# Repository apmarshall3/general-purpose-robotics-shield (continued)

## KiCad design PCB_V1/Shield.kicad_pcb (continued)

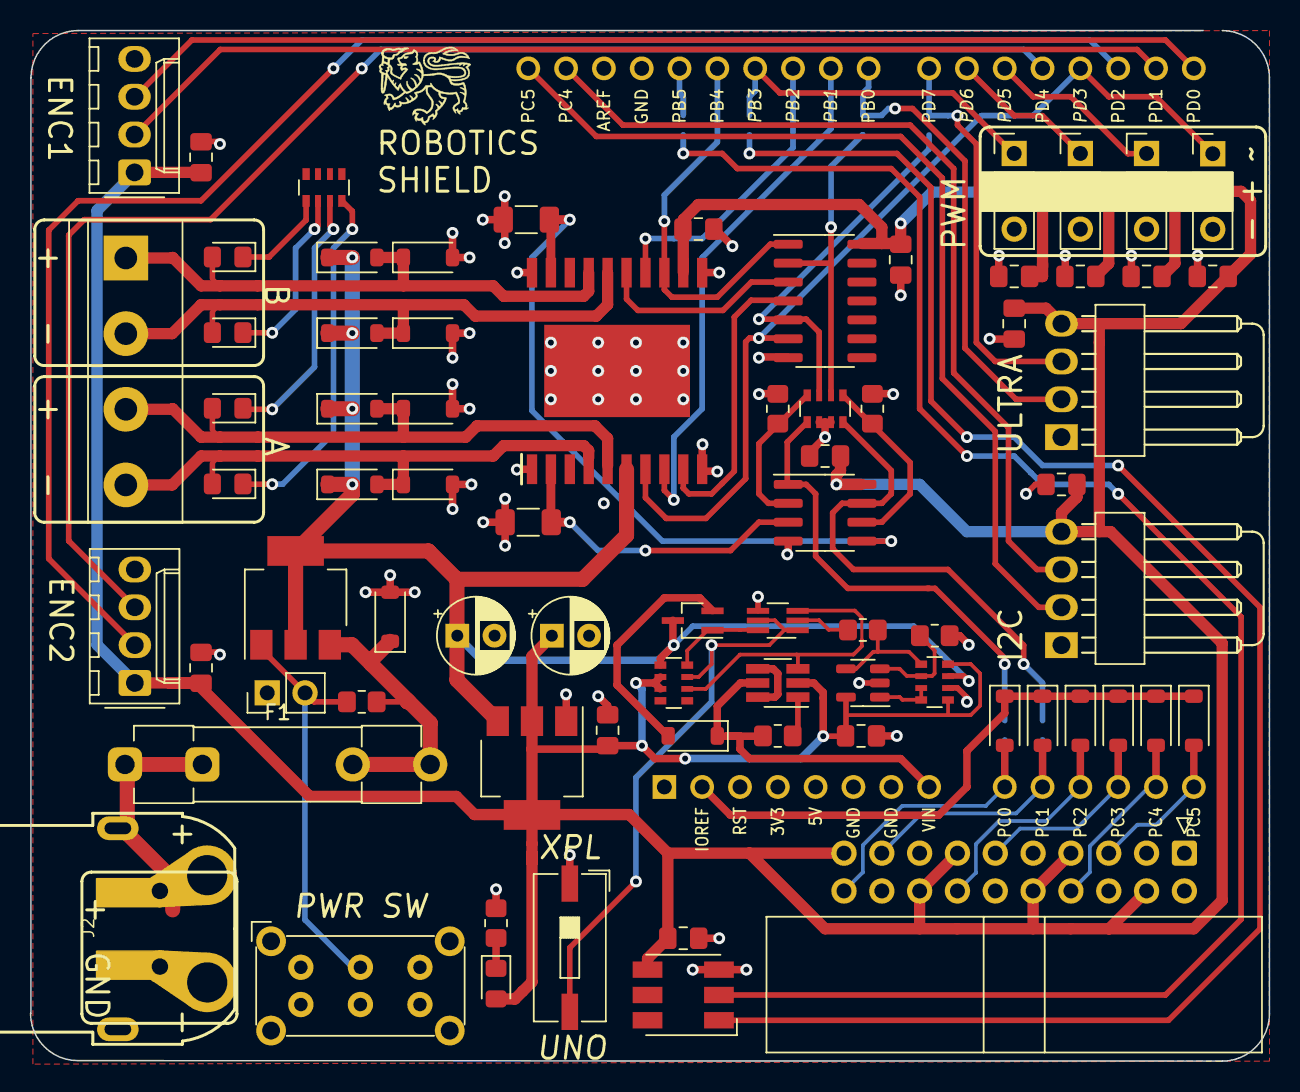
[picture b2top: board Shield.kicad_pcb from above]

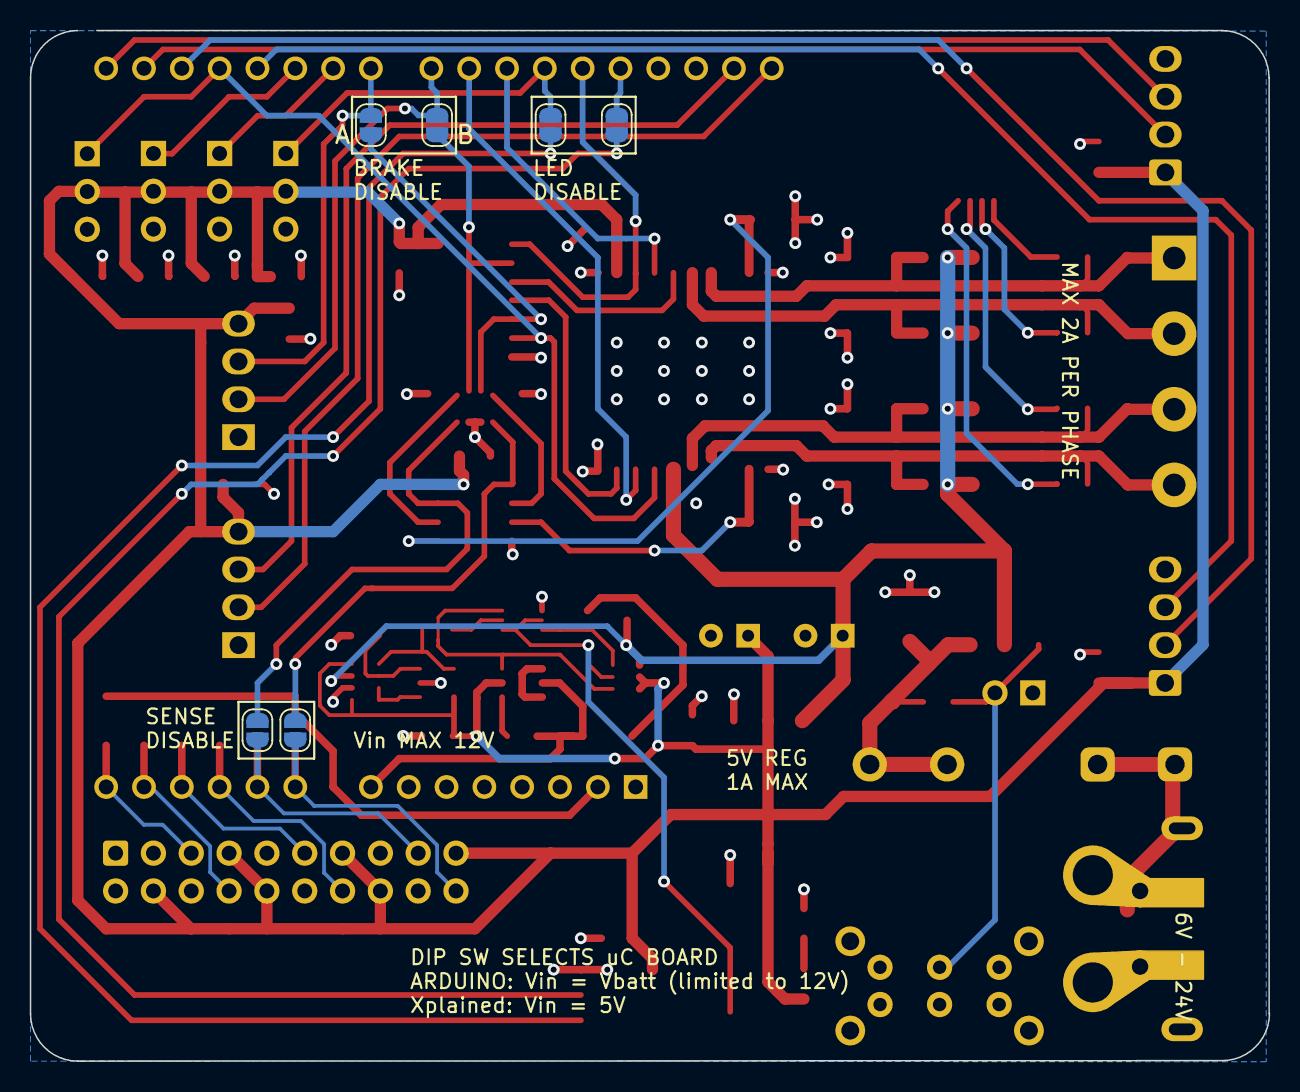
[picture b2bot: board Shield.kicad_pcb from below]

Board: 2 copper layers, 83.2 x 69.2 mm, 82 parts (7 on the bottom side), 61 nets.

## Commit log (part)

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2024-03-01 Tidied schematic and layout, added indicators and silkscreen notes
2024-03-01 Fixed links between schem and pcb, re-added annotation, updated L298 footprint and updated layout
2024-03-05 Added comment
2024-03-12 Ricks Changes
2024-03-20 update to v2
    Update to V2 with offset header
2024-03-21 Minor changes to layout
    fixed overlapping silk and courtyards
    tweaked track layouts to clear disconencted edges and imporve some clearances
    fixed board outline
2024-03-21 Update
    Added gnd via's, and caps for LP filter on analog in's
2024-04-09 updates
    Bug fixes
2024-04-11 V2 update
    Foot prints, component selection, etc.
2024-04-12 Tidied schematic and removed old comments
2024-04-12 Changed to vertical conn
2024-04-12 Changed to vertical connector
2024-04-12 Minor changes to layout
    Made placement of connectors more consistent.
    Relocated SMT electrolytic caps to allow more space
    Made IN1 layer 5V
    Tidied routing of motor driver outputs and swapped to using pours. Moved vias out from under components.
    Adjusted power supply component placement to allow more space and smaller loop areas.
2024-04-12 Swapped ENC1 and ENC2 so they match the motor they are next to
2024-04-12 Layout changes
    Rearranged power supply components to better use space, removed components where possible from gap between offset headers.
    Moved offset headers slightly to become aligned.
    Added copper pours for high current nets
    Removed F.Cu 5V tracks, inner layer plane is now used instead.
    Swapped ENC1 and ENC2 to be consistent with motor phases.
    Added silkscreen indicators for analogue, and updated power output header silk to match others.
